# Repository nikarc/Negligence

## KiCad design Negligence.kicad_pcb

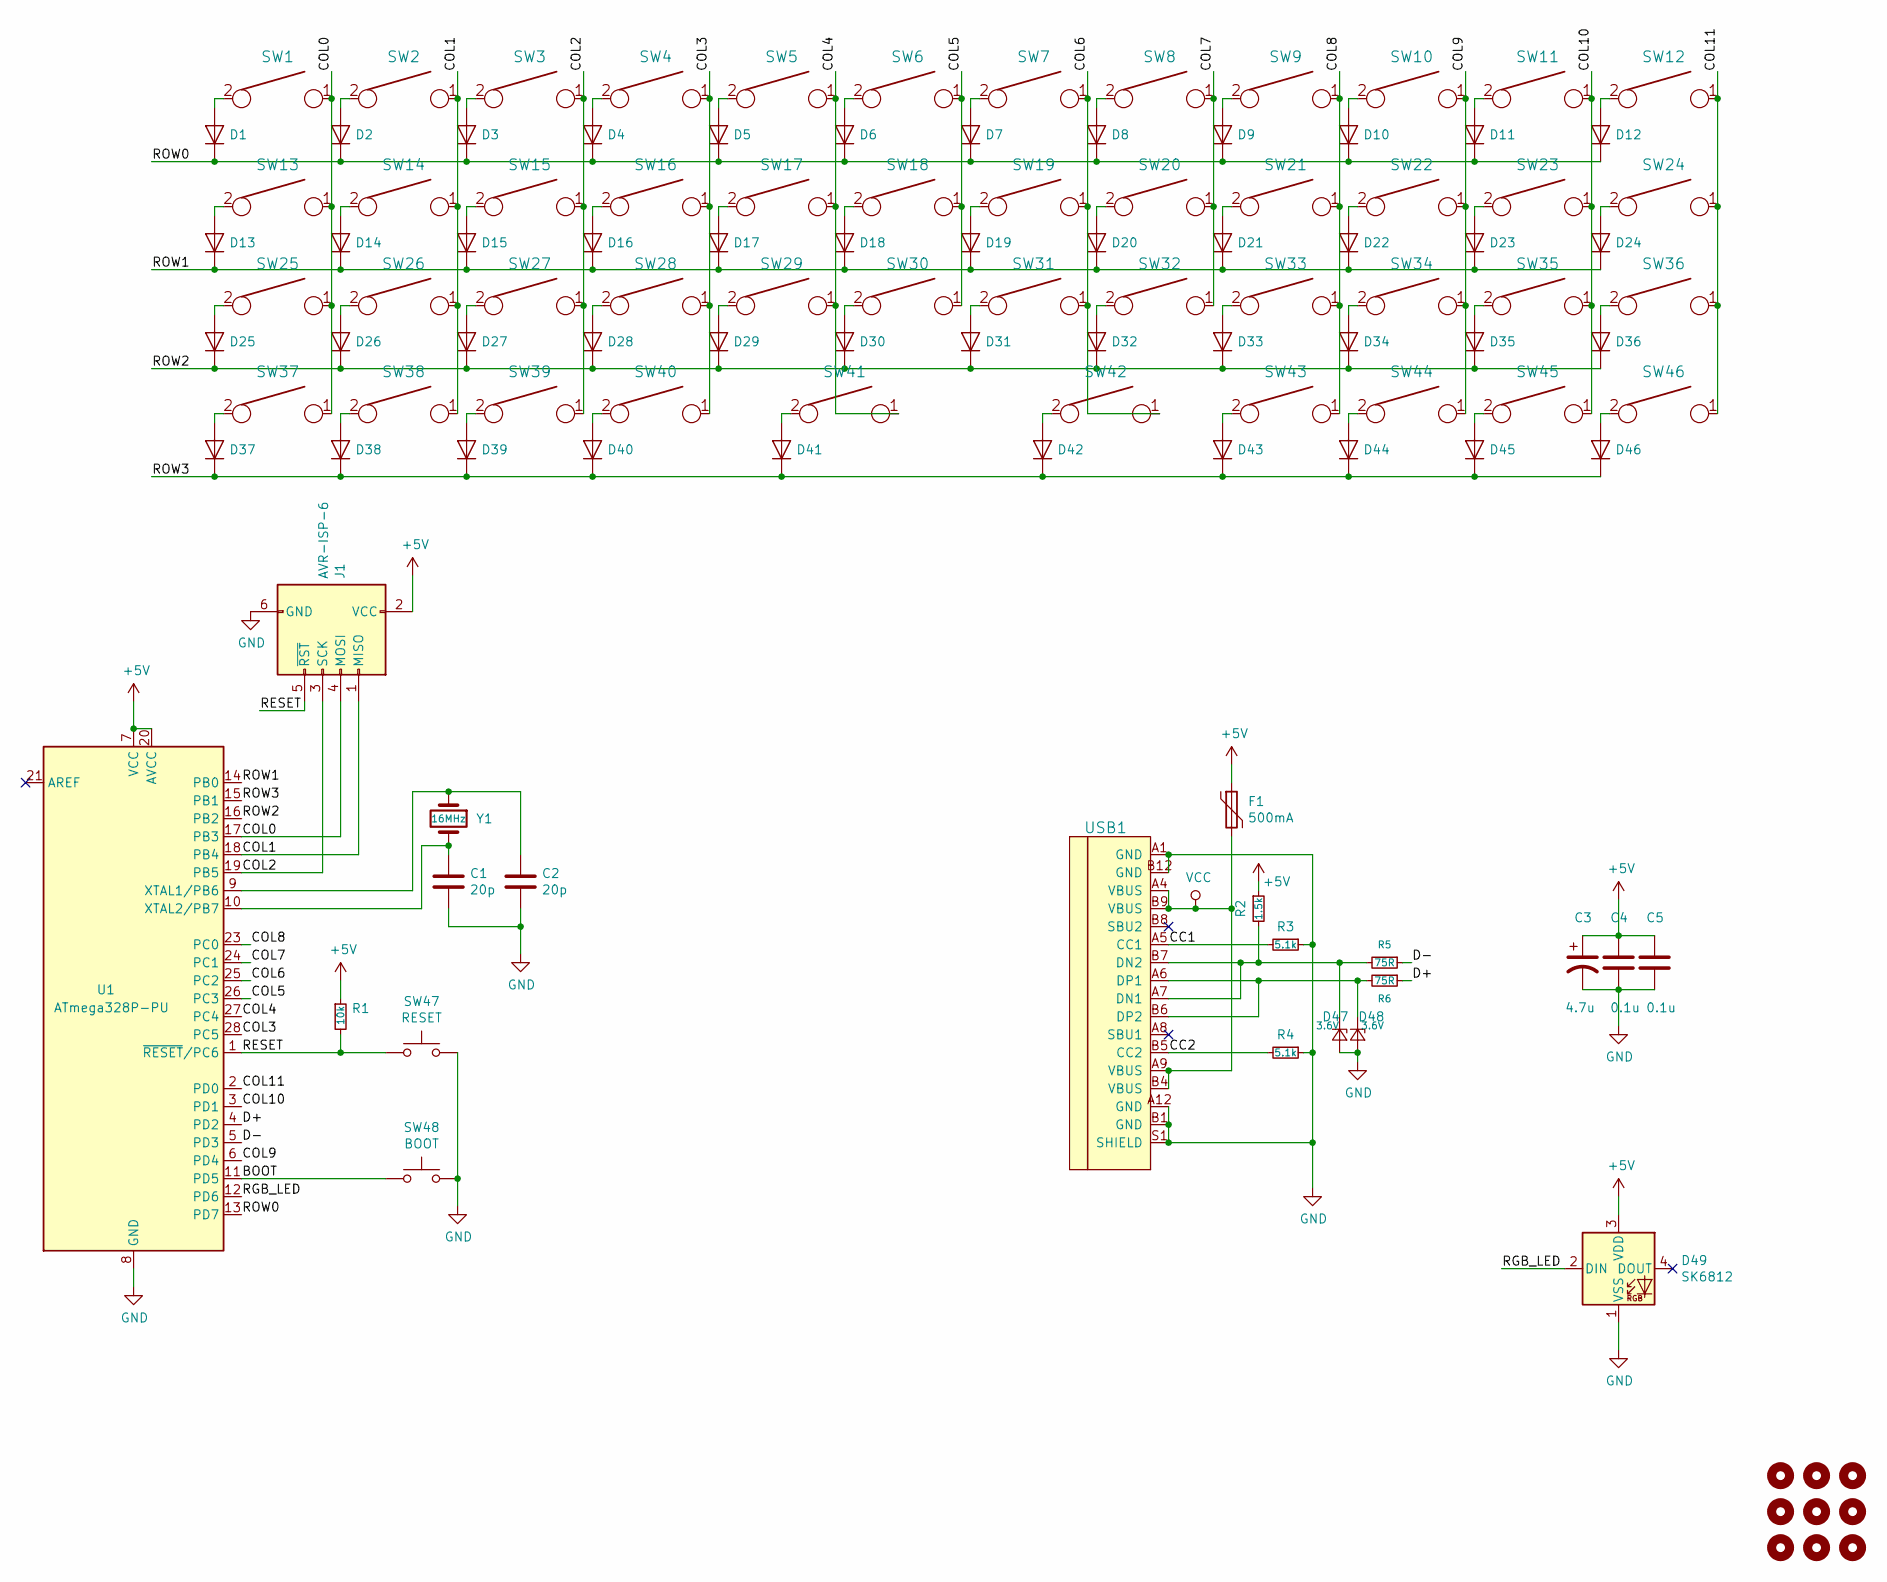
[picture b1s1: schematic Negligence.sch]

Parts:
C1, C2: 20p; C_Disc_D3.0mm_W1.6mm_P2.50mm
C3: 4.7u; CP_Radial_D4.0mm_P1.50mm
C4, C5: 0.1u; C_Disc_D4.3mm_W1.9mm_P5.00mm
D1, D2, D3, D4, D5, D6, D7, D8, D9, D10, D11, D12, D13, D14, D15, D16, D17, D18, D19, D20, D21, D22, D23, D24, D25, D26, D27, D28, D29, D30, D31, D32, D33, D34, D35, D36, D37, D38, D39, D40, D41, D42, D43, D44, D45, D46: 1N4148; D_DO-35_SOD27_P5.08mm_Horizontal
D47, D48: 3.6V; D_DO-35_SOD27_P5.08mm_Horizontal
D49: SK6812; LED_SK6812_PLCC4_5.0x5.0mm_P3.2mm
F1: 500mA; polyfuse_5.1mm
H1, H2, H3, H4, H5, H6, H7, H8, H9: MountingHole; MountingHole_2.2mm_M2
J1: AVR-ISP-6; AVR_ICSP_3x2
R1: 10k; R_Axial_DIN0204_L3.6mm_D1.6mm_P5.08mm_Horizontal
R2: 1.5k; R_Axial_DIN0204_L3.6mm_D1.6mm_P5.08mm_Horizontal
R3, R4: 5.1k; R_Axial_DIN0204_L3.6mm_D1.6mm_P5.08mm_Horizontal
R5, R6: 75R; R_Axial_DIN0204_L3.6mm_D1.6mm_P5.08mm_Horizontal
SW1, SW2, SW3, SW4, SW5, SW6, SW7, SW8, SW9, SW10, SW11, SW12, SW13, SW14, SW15, SW16, SW17, SW18, SW19, SW20, SW21, SW22, SW23, SW24, SW25, SW26, SW27, SW28, SW29, SW30, SW31, SW32, SW33, SW34, SW35, SW36, SW37, SW38, SW39, SW40, SW43, SW44, SW45, SW46: keyboard_parts_KEYSW; SW_Cherry_MX1A_1.00u_PCB-NOSCREEN
SW41, SW42: keyboard_parts_KEYSW; SW_Cherry_MX1A_2.00u_PCBNOSCREEN
SW47: RESET; SW_PUSH_6mm
SW48: BOOT; SW_PUSH_6mm
U1: ATmega328P-PU; DIP-28_W7.62mm
USB1: USB_C_GCT_USB4085-Type-C; USB_C_GCT_USB4085
Y1: 16MHz; Crystal_HC49-4H_Vertical

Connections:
+5V: C3.1, C4.1, C5.1, D49.3 (VDD), F1.1, J1.2 (VCC), R1.1, R2.1, U1.7 (VCC), U1.20 (AVCC); also elsewhere on the board
/BOOT: SW48.1, U1.11 (PD5)
/CC1: R3.2, USB1.A5 (CC1)
/CC2: R4.2, USB1.B5 (CC2)
/COL0: J1.4 (MOSI), SW1.1, SW13.1, SW25.1, SW37.1, U1.17 (PB3)
/COL1: J1.1 (MISO), SW2.1, SW14.1, SW26.1, SW38.1, U1.18 (PB4)
/COL2: J1.3 (SCK), SW3.1, SW15.1, SW27.1, SW39.1, U1.19 (PB5)
/COL3: SW4.1, SW16.1, SW28.1, SW40.1, U1.28 (PC5)
/COL4: SW5.1, SW17.1, SW29.1, SW41.1, U1.27 (PC4)
/COL5: SW6.1, SW18.1, SW30.1, U1.26 (PC3)
/COL6: SW7.1, SW19.1, SW31.1, SW42.1, U1.25 (PC2)
/COL7: SW8.1, SW20.1, SW32.1, U1.24 (PC1)
/COL8: SW9.1, SW21.1, SW33.1, SW43.1, U1.23 (PC0)
/COL9: SW10.1, SW22.1, SW34.1, SW44.1, U1.6 (PD4)
/COL10: SW11.1, SW23.1, SW35.1, SW45.1, U1.3 (PD1)
/COL11: SW12.1, SW24.1, SW36.1, SW46.1, U1.2 (PD0)
/D+: R6.1, U1.4 (PD2); also elsewhere on the board
/D-: R5.1, U1.5 (PD3); also elsewhere on the board
/RESET: J1.5 (~RST), R1.2, SW47.1, U1.1 (~RESET~/PC6)
/RGB_LED: D49.2 (DIN), U1.12 (PD6)
/ROW0: D1.1 (K), D2.1 (K), D3.1 (K), D4.1 (K), D5.1 (K), D6.1 (K), D7.1 (K), D8.1 (K), D9.1 (K), D10.1 (K), D11.1 (K), D12.1 (K), U1.13 (PD7)
/ROW1: D13.1 (K), D14.1 (K), D15.1 (K), D16.1 (K), D17.1 (K), D18.1 (K), D19.1 (K), D20.1 (K), D21.1 (K), D22.1 (K), D23.1 (K), D24.1 (K), U1.14 (PB0)
/ROW2: D25.1 (K), D26.1 (K), D27.1 (K), D28.1 (K), D29.1 (K), D30.1 (K), D31.1 (K), D32.1 (K), D33.1 (K), D34.1 (K), D35.1 (K), D36.1 (K), U1.16 (PB2)
/ROW3: D37.1 (K), D38.1 (K), D39.1 (K), D40.1 (K), D41.1 (K), D42.1 (K), D43.1 (K), D44.1 (K), D45.1 (K), D46.1 (K), U1.15 (PB1)
GND: C1.2, C2.2, C3.2, C4.2, C5.2, D47.2 (A), D48.2 (A), D49.1 (VSS), J1.6 (GND), R3.1, R4.1, SW47.2, SW48.2, U1.8 (GND), U1.22 (GND), USB1.A1 (GND), USB1.A12 (GND), USB1.B1 (GND), USB1.B12 (GND), USB1.S1 (SHIELD)
unnamed: C1.1, U1.10 (XTAL2/PB7), Y1.2
unnamed: C2.1, U1.9 (XTAL1/PB6), Y1.1
unnamed: D1.2 (A), SW1.2
unnamed: D2.2 (A), SW2.2
unnamed: D3.2 (A), SW3.2
unnamed: D4.2 (A), SW4.2
unnamed: D5.2 (A), SW5.2
unnamed: D6.2 (A), SW6.2
unnamed: D7.2 (A), SW7.2
unnamed: D8.2 (A), SW8.2
unnamed: D9.2 (A), SW9.2
unnamed: D10.2 (A), SW10.2
unnamed: D11.2 (A), SW11.2
unnamed: D12.2 (A), SW12.2
unnamed: D13.2 (A), SW13.2
unnamed: D14.2 (A), SW14.2
unnamed: D15.2 (A), SW15.2
unnamed: D16.2 (A), SW16.2
unnamed: D17.2 (A), SW17.2
unnamed: D18.2 (A), SW18.2
unnamed: D19.2 (A), SW19.2
unnamed: D20.2 (A), SW20.2
unnamed: D21.2 (A), SW21.2
unnamed: D22.2 (A), SW22.2
unnamed: D23.2 (A), SW23.2
unnamed: D24.2 (A), SW24.2
unnamed: D25.2 (A), SW25.2
unnamed: D26.2 (A), SW26.2
unnamed: D27.2 (A), SW27.2
unnamed: D28.2 (A), SW28.2
unnamed: D29.2 (A), SW29.2
unnamed: D30.2 (A), SW30.2
unnamed: D31.2 (A), SW31.2
unnamed: D32.2 (A), SW32.2
unnamed: D33.2 (A), SW33.2
unnamed: D34.2 (A), SW34.2
unnamed: D35.2 (A), SW35.2
unnamed: D36.2 (A), SW36.2
unnamed: D37.2 (A), SW37.2
unnamed: D38.2 (A), SW38.2
unnamed: D39.2 (A), SW39.2
unnamed: D40.2 (A), SW40.2
unnamed: D41.2 (A), SW41.2
unnamed: D42.2 (A), SW42.2
unnamed: D43.2 (A), SW43.2
unnamed: D44.2 (A), SW44.2
unnamed: D45.2 (A), SW45.2
unnamed: D46.2 (A), SW46.2
unnamed 73: D47.1 (K), R2.2, R5.2, USB1.A7 (DN1), USB1.B7 (DN2); also elsewhere on the board
unnamed 74: D48.1 (K), R6.2, USB1.A6 (DP1), USB1.B6 (DP2); also elsewhere on the board
VCC: F1.2, USB1.A4 (VBUS), USB1.A9 (VBUS), USB1.B4 (VBUS), USB1.B9 (VBUS)

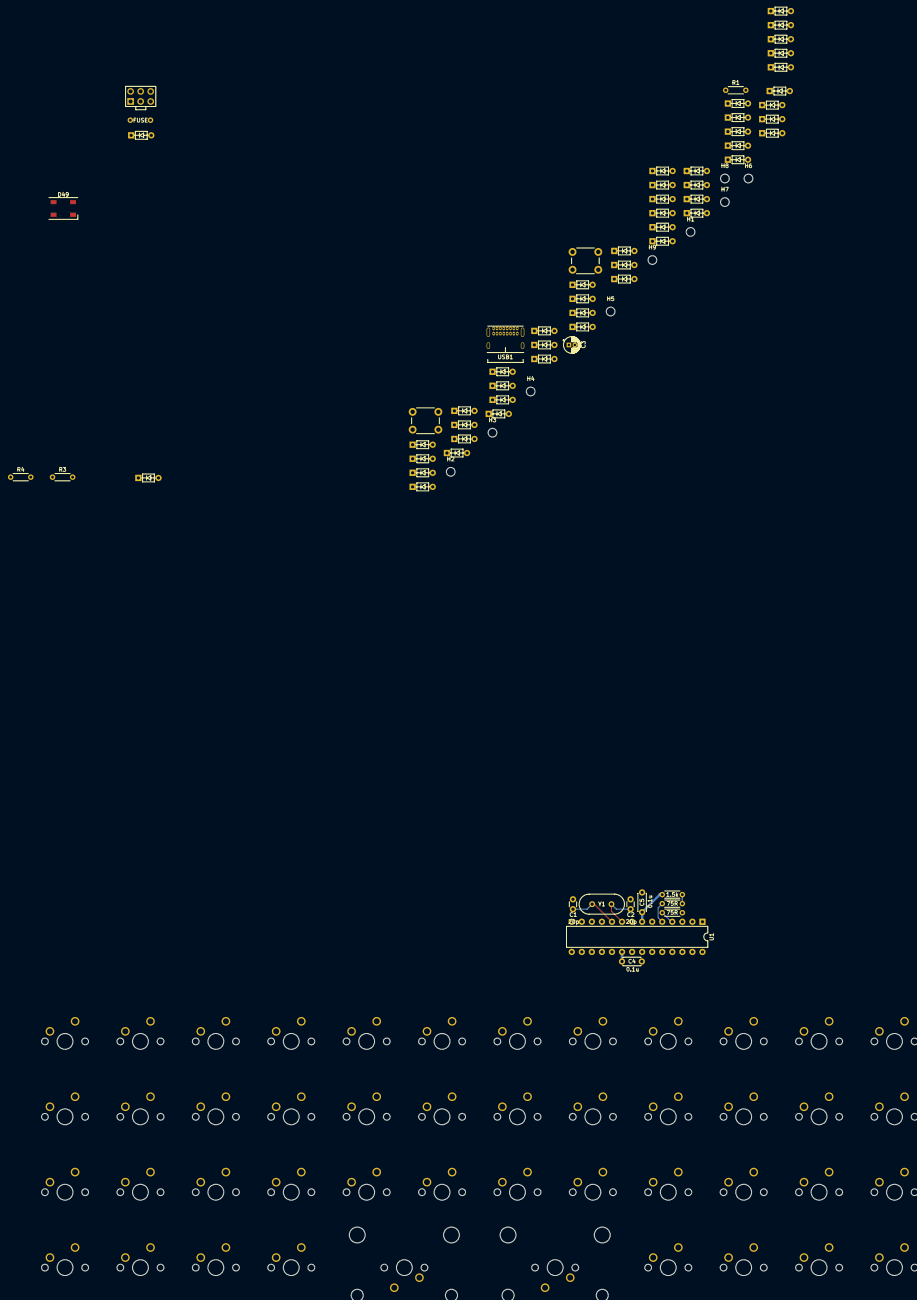
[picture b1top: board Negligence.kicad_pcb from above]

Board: 2 copper layers, 122 parts (0 on the bottom side), 76 nets.

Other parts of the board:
1.5k: 1.5k; R_Axial_DIN0204_L3.6mm_D1.6mm_P5.08mm_Horizontal
75R, 75R#2: 75R; R_Axial_DIN0204_L3.6mm_D1.6mm_P5.08mm_Horizontal

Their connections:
+5V: 1.5k.1; also elsewhere on the board
/D+: 75R.1; also elsewhere on the board
/D-: 75R#2.1; also elsewhere on the board
unnamed 73: 1.5k.2, 75R#2.2; also elsewhere on the board
unnamed 74: 75R.2; also elsewhere on the board

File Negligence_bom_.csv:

Component,Description,Part,References,Value,Footprint,Quantity Per PCB,Datasheet
1,Unpolarized capacitor,C,C4 C5,0.1u,C_Disc_D4.3mm_W1.9mm_P5.00mm,2,~
2,Unpolarized capacitor,C,C1 C2,20p,C_Disc_D3.0mm_W1.6mm_P2.50mm,2,~
3,"Polarized capacitor, US symbol",CP1,C3,4.7u,CP_Radial_D4.0mm_P1.50mm,1,~
4,"100V 0.15A standard switching diode, DO-35",1N4148,D1 D2 D3 D4 D5 D6 D7 D8 D9 D10 D11 D12 D13 D14 D15 D16 D17 D18 D19 D20 D21 D22 D23 D24 D25 D26 D27 D28 D29 D30 D31 D32 D33 D34 D35 D36 D37 D38 D39 D40 D41 D42 D43 D44 D45 D46,1N4148,D_DO-35_SOD27_P5.08mm_Horizontal,46,https://assets.nexperia.com/documents/data-sheet/1N4148_1N4448.pdf
5,,Device_D_Zener_Small,D47 D48,3.6V,D_DO-35_SOD27_P5.08mm_Horizontal,2,
6,RGB LED with integrated controller,SK6812,D49,SK6812,LED_SK6812_PLCC4_5.0x5.0mm_P3.2mm,1,https://cdn-shop.adafruit.com/product-files/1138/SK6812+LED+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
7,"Resettable fuse, polymeric positive temperature coefficient",Polyfuse,F1,500mA,polyfuse_5.1mm,1,~
8,Atmel 6-pin ISP connector,AVR-ISP-6,J1,AVR-ISP-6,AVR_ICSP_3x2,1, ~
9,"Resistor, small symbol",R_Small,R2,1.5k,R_Axial_DIN0204_L3.6mm_D1.6mm_P7.62mm_Horizontal,1,~
10,"Resistor, small symbol",R_Small,R1,10k,R_Axial_DIN0204_L3.6mm_D1.6mm_P7.62mm_Horizontal,1,~
11,"Resistor, small symbol",R_Small,R3 R4,5.1k,R_Axial_DIN0204_L3.6mm_D1.6mm_P7.62mm_Horizontal,2,~
12,"Resistor, small symbol",R_Small,R5 R6,75R,R_Axial_DIN0204_L3.6mm_D1.6mm_P7.62mm_Horizontal,2,~
13,"Push button switch, generic, two pins",SW_Push,SW48,BOOT,SW_PUSH_6mm,1,~
14,"Push button switch, generic, two pins",SW_Push,SW47,RESET,SW_PUSH_6mm,1,~
15,,keyboard_parts_KEYSW,SW1 SW2 SW3 SW4 SW5 SW6 SW7 SW8 SW9 SW10 SW11 SW12 SW13 SW14 SW15 SW16 SW17 SW18 SW19 SW20 SW21 SW22 SW23 SW24 SW25 SW26 SW27 SW28 SW29 SW30 SW31 SW32 SW33 SW34 SW35 SW36 SW37 SW38 SW39 SW40 SW43 SW44 SW45 SW46,keyboard_parts_KEYSW,SW_Cherry_MX1A_1.00u_PCB-NOSCREEN,44,
16,,keyboard_parts_KEYSW,SW41 SW42,keyboard_parts_KEYSW,SW_Cherry_MX1A_2.00u_PCBNOSCREEN,2,
17,"20MHz, 32kB Flash, 2kB SRAM, 1kB EEPROM, DIP-28",ATmega328P-PU,U1,ATmega328P-PU,DIP-28_W7.62mm,1,http://ww1.microchip.com/downloads/en/DeviceDoc/ATmega328_P%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
18,,USB_C_GCT_USB4085-Type-C,USB1,USB_C_GCT_USB4085-Type-C,USB_C_GCT_USB4085,1,
19,,Device_Crystal,Y1,16MHz,Crystal_HC49-4H_Vertical,1,





Component Groups:,19
Component Count:,113
Fitted Components:,113
Number of PCBs:,1
Total components:,113
Schematic Version:,
Schematic Date:,
PCB Variant:,default
BoM Date:,"Tuesday, December 03, 2019 at 01:21:27 PM"
Schematic Source:,/Users/nicholasarcuri/Documents/kicad/Negligence/Negligence.sch
KiCad Version:,Eeschema (5.1.4-0-10_14)

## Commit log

2019-11-25 Schema setup
2019-11-25 Layout switches on pcb
2019-11-25 Start wiring switches
2019-11-25 More key sw traces
2019-11-25 Finish diode wiring
2019-11-26 Space saving
2019-11-26 Start MCU wiring
2019-11-26 Finish mcu
2019-11-26 Edge cuts and place components on board
2019-11-27 Wire USB, various
2019-11-27 Start diode rows
2019-11-27 More diode routing
2019-11-27 Add GND vias
2019-11-27 Fill zone cleanup
2019-11-28 Redo power section
2019-11-29 Fully wired
2019-11-29 Zone fills
2019-11-29 Parts silk screen
2019-11-29 Mounting holes
2019-12-01 CSV/gerber
2019-12-03 Add addressable led
2019-12-03 Cleanup, gerber/drill files
2019-12-03 Generate BOM
2020-04-06 various updates
